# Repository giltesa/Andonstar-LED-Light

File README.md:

# Andonstar LED Light

This is an electronic circuit made of aluminum to build a light that attaches to the Andonstar ADSM201 microscope.

Here is more information, but it is in Spanish:
[**Lampara LED para microscopio Andonstar ADSM201**](https://giltesa.com/2018/06/20/lampara-led-para-microscopio-andonstar-adsm201).

Youtube Video:

## License

This project is licensed under the license **Creative Commons** of type: **[Attribution-NonCommercial-ShareAlike 4.0 International (CC BY-NC-SA 4.0) ](https://creativecommons.org/licenses/by-nc-sa/4.0/)**. Check the file [LICENSE.md](LICENSE.md) for more information.

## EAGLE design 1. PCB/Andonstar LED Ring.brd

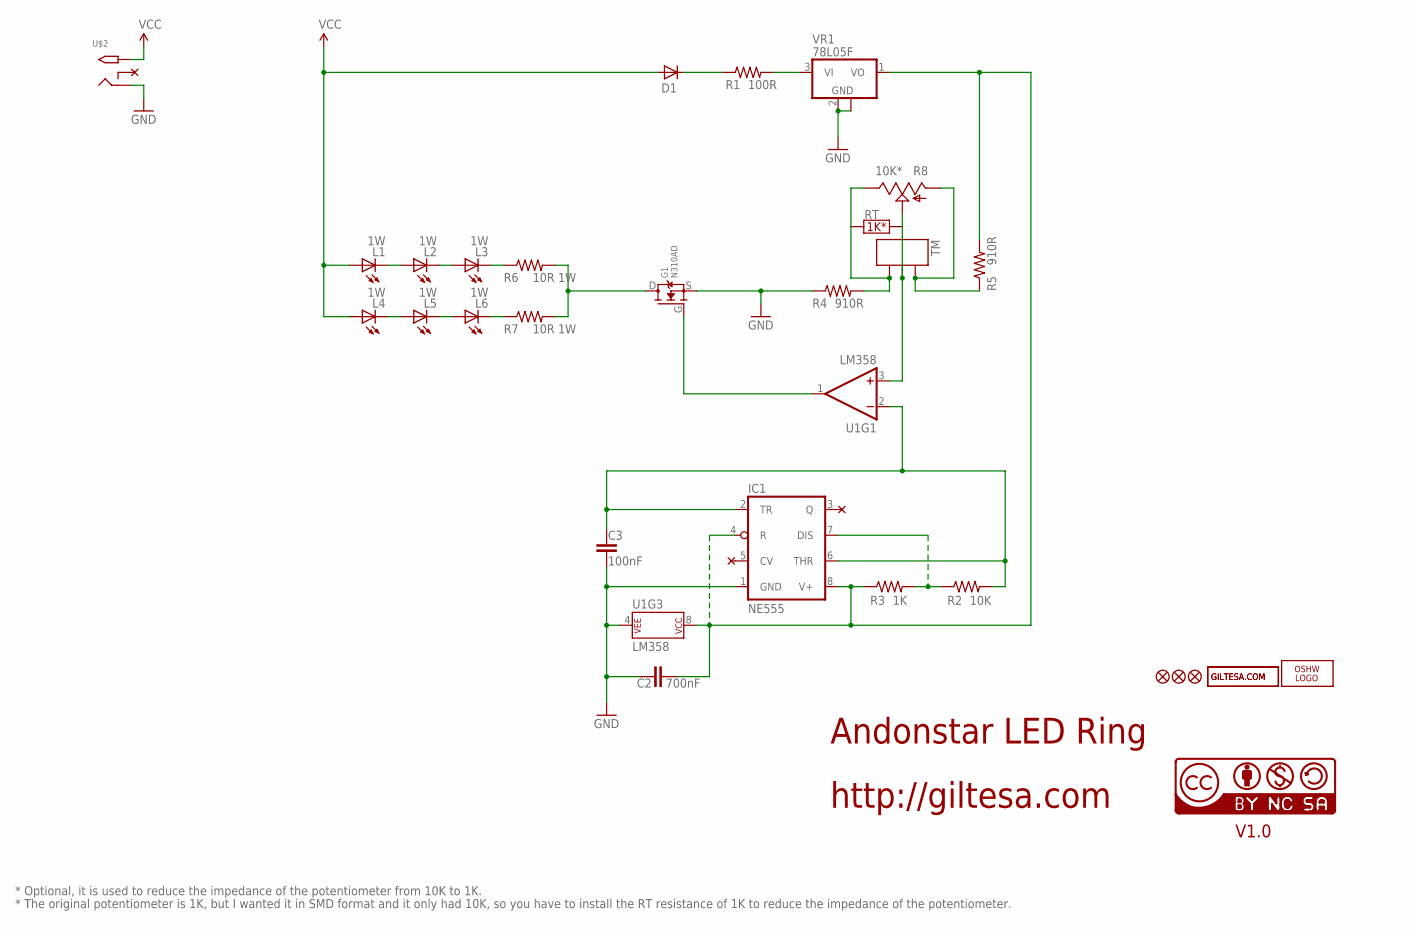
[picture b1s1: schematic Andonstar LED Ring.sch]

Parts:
C2: 700nF; C0603
C3: 100nF; C0603
D1: DIODE-GF1; GF1
G1: N310AD; TO-252
IC1: NE555; SO08
L1, L2, L3, L4, L5, L6: 1W; LED_Z_POWER
LOGO1: OSHW_LOGO_FILLX0150-NT; OSHW_FILLX150_NOTEXT
R1: 100R; R1206
R2: 10K; R0603
R3: 1K; R0603
R4, R5: 910R; R0603
R6, R7: 10R 1W; R2512
R8: 10K*; TRIMPOT_SMD_16MM
TM: 1X03; 1X03_SMD
U1: LM358; SO08
U$1: GILTESA.COM_MASK
U$2: 2.1MMJACKSMT; DCJACK_2MM_SMT
U$6, U$7, U$14: FIDUCIAL1X2; FIDUCIAL-1X2
U$8: GILTESA.COM_COPPER_STOP
U$20: CC-NC-BCNIX; CC-NC-B_NIX
VR1: 78L05F; SOT89

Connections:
GND: C2.2, C3.1, G1.S, IC1.1 (GND), R4.1, U1.4 (P$V-), U$2.GND (RING), VR1.2 (GND), VR1.2@1 (GND)
unnamed: L5.C, L6.A
unnamed: L4.C, L5.A
unnamed: L2.C, L3.A
unnamed: L1.C, L2.A
unnamed: L3.C, R6.1
unnamed: L6.C, R7.1
unnamed: IC1.7 (DIS), R2.1, R3.2
unnamed: G1.D, R6.2, R7.2
unnamed: C3.2, IC1.2 (TR), IC1.6 (THR), R2.2, U1.2 (-IN)
unnamed: R8.S, TM.2, U1.3 (+IN)
unnamed: R5.1, R8.A, TM.3
unnamed: R4.2, R8.B, TM.1
unnamed: R1.2, VR1.3 (VI)
unnamed: C2.1, IC1.4 (R), IC1.8 (V+), R3.1, R5.2, U1.8 (P$V+), VR1.1 (VO)
unnamed: D1.C, R1.1
unnamed: G1.G, U1.1 (OUT)
VCC: D1.A, L1.A, L4.A, U$2.PWR2 (TIP)

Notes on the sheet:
Andonstar LED Ring
http://giltesa.com
V1.0
1K*
* The original potentiometer is 1K, but I wanted it in SMD format and it only had 10K, so you have to install the RT resistance of 1K to reduce the impedance of the potentiometer.
* Optional, it is used to reduce the impedance of the potentiometer from 10K to 1K.

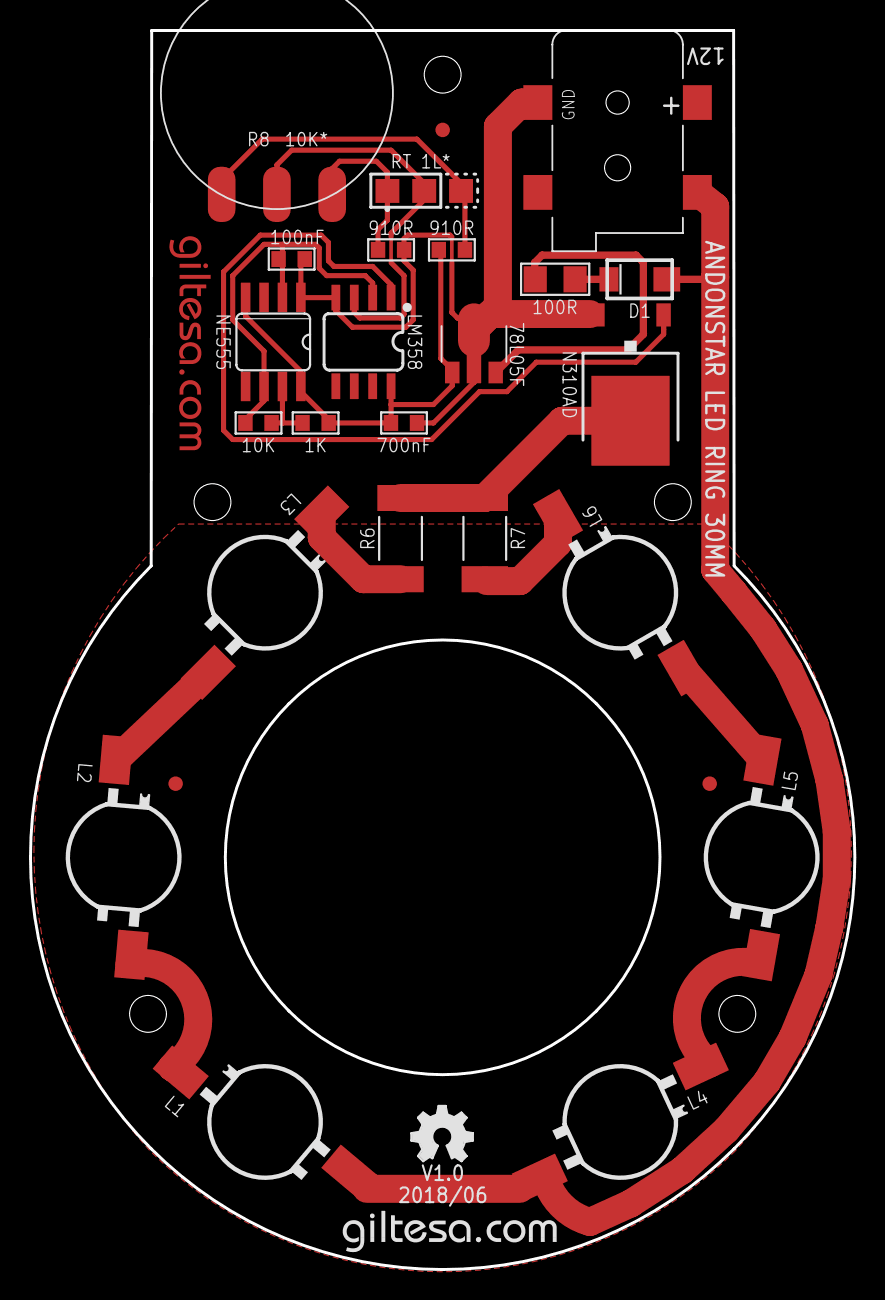
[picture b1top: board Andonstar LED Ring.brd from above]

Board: 2 copper layers, 56.9 x 85.4 mm, 30 parts (0 on the bottom side), 18 nets.

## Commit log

2018-06-21 :tada: Added .gitattributes & .gitignore files
2018-06-21 Upload v1.0

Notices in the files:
parts and their libraries:
SparkFun-IC-Amplifiers: Licensing: Creative Commons ShareAlike 4.0 International - https://creativecommons.org/licenses/by-sa/4.0
cc-by-nc-sa: All hardware is licensed under the Creative Commons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
